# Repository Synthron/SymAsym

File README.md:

# SymAsym

High Power Audio Amplifier based on the Red Devil SymAsym PCBs from audiopcb.de

For complete system schematic of a stereo amplifier, refer to _**Overview_Schematic.pdf**_

Specs:  

- 350W @ 4 Ohm
- 185W @ 8 Ohm

Zusätzliches Empfangsmodul "Up2Stream Pro V3" empfohlen.

## Warenkörbe Reichelt

- [Black Devil Amplifier](https://www.reichelt.de/my/2100439) 
  - 2x benötigt für Stereo
  - Extra Kühlkörper benötigt - siehe unten
- [Netzfilter und Softstart](https://www.reichelt.de/my/2100481)
  - designed für Stereo, für Mono in der Mitte teilen
- [VU-Meter](https://www.reichelt.de/my/2100492)
- [Digital-Support](https://www.reichelt.de/my/2100502)
  - Extra OLED benötigt (I2C-Schnittstelle, siehe unten)

## Einstellung

- Vor Inbetriebnahme Poti so drehen, dass zwischen unterem Pin R24 und linkem Pin R9 500 Ohm Widerstand gemessen werden.  
- Kurzschlussbrücke am Signaleingang einstecken für Abgleich.  
- Spannung anschließen und am Ausgang messen, sollte ca. 0V betragen.  
- Jetzt Poti so lange drehen, bis zwischen TP1->TP3 und TP2->TP3 jeweils 55mV (0,055V) anliegen.  
- Fertig

## Anmerkungen

### Amplifier

**Wichtig!!!**  
Der Warenkorb ist nur für eine Platine! Für einen Stereo-Verstärker bitte zwei mal bestellen!

**2N5551 und 2N5401 Transistoren:**  
Anstatt passender Anzahl sind in den Warenkörben zu viele eingetragen. Dadurch hat man genug Transistoren um die drei notwendingen Paare matchen zu können. Siehe Schaltplan, welche Transistoren gematcht sein müssen.

**Kühlkörper**  
Die Leistungstransistoren müssen mit einer Glimmerscheibe gegen den Kühlkörper isoliert werden. Elektrisch isolierende Wärmeleitpads sind auch ok. Keinesfalls nur Wärmeleitpaste benutzen!

Beispiel [Silikonfolie](https://www.reichelt.de/silikon-isolierfolie-200x200x0-18mm-si-4018-p35416.html?&trstct=pos_1&nbc=1); [Glimmer TO220](https://www.reichelt.de/glimmerscheibe-fuer-gehaeuse-to-220-glimmer-to-220-p8194.html?&trstct=pos_5&nbc=1)  
Die Isolierbuchsen (im Warenkorb) müssen bei den MJE-Transistoren (TO220) verwendet werden!

**R7**  
Der Widerstand R7 muss mit 10 Windungen 0,7mm - 1mm Kupferlackdraht umwickelt werden, dieser wird an die Pins des Widerstandes angelötet. 

---

### Netzfilter und Softstart

Die Sicherungshalter sind einzelne Federn, beim Einlöten mit 5x20mm Feinsicherung ausrichten.  

---

### VU-Meter

Vorsicht: LEDs und Potis auf Rückseite und alles außer LEDs/Terminals ist SMD.

Zum Abgleichen: maximale gewollte Lautstärke aufdrehen, mit Potis so einstellen, dass nur die erste rote LED leuchtet.  
Für beide Kanäle einzeln einrichten.

---

### Digital-Support

Die Sicherungshalter sind einzelne Federn, beim Einlöten mit 5x20mm Feinsicherung ausrichten.  
Fast alle Bauteile sind SMD.

NTC-Widerstände werden direkt an die Kühlkörper geschraubt!

Die Bedienung erfolg neben dem Drehencoder über ein OLED, original wird [dieses](https://www.reichelt.de/entwicklerboards-display-oled-2-42-128x64-pixel-debo-oled-2-42-p335005.html?&trstct=pos_3&nbc=1) benutzt.

Wenn **kein** Up2Stream benutzt wird, PD2 und GND verbinden.

Konfiguration für Standard Eingang:

| Standard Eingang      | PD3 | PD4 |
|-----------------------|:---:|:---:|
| Kein Eingang          | GND | GND |
| Eingang 1 (Klinke)    |  5V | GND |
| Eingang 2 (Cinch)     | GND |  5V |
| Eingang 3 (Up2Stream) |  5V |  5V |

Der Kanal kann über den Drehencoder jederzeit geändert werden.  
Wenn das Up2Stream-Modul angeschlossen ist, werden je nach Möglichkeit aktuelle Song-Infos auf dem OLED angezeigt. 

---

### Gehäuse

Beim Entwurf wurde alles auf [dieses Gehäuse](https://www.reichelt.de/19-rack-gehaeuse-3-he-sin-3-he-sw-p247242.html?&trstct=pos_0&nbc=1) ausgelegt.

---

### Kühlkörper

Pro Verstärkerplatine sollte ein Kühlkörper mit maximal 0,5K/W vorgesehen werden. Für das oben genannte Gehäuse bietet sich [dieser Kühlkörper](https://www.reichelt.de/kuehlkoerper-100-mm-alu-0-4-k-w-sk-56-100-sa-p227981.html?&trstct=pol_5&nbc=1) an. Er ist 1cm zu lang, das kann aber zur Not gekürzt werden.

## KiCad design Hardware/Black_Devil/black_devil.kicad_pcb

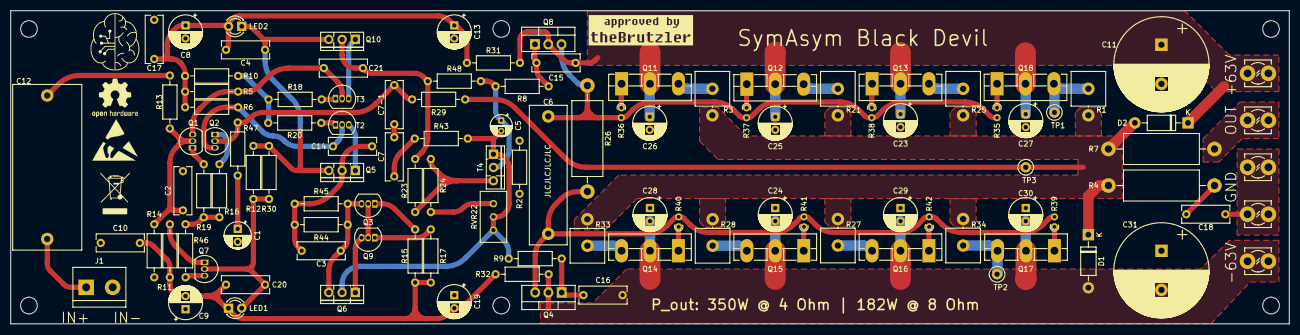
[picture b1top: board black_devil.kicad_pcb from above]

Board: 2 copper layers, 245.0 x 60.0 mm, 113 parts (0 on the bottom side), 60 nets.

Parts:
C1: 330µF/16V; CP_Radial_D5.0mm_P2.50mm
C2: 680p; C_Rect_L9.0mm_W3.2mm_P7.50mm_MKT
C3, C4, C10, C17, C20: 100n; C_Rect_L9.0mm_W3.2mm_P7.50mm_MKT
C5: 47µ/25V; CP_Radial_D4.0mm_P2.00mm
C6: 680n; C_Rect_L26.5mm_W7.0mm_P22.50mm_MKS4
C7, C7-1: 10p; C_Rect_L9.0mm_W3.2mm_P7.50mm_MKT
C8, C9, C13, C19, C23, C24, C25, C26, C27, C28, C29, C30: 22µ 100V; CP_Radial_D6.3mm_P2.50mm
C11, C31: 680µ 100V; CP_Radial_D18.0mm_P7.50mm
C12: 10µ; C_Rect_L31.5mm_W13.0mm_P27.50mm_MKS4
C14, C15, C16, C21: 100p; C_Rect_L9.0mm_W3.2mm_P7.50mm_MKT
C18: 47n; C_Rect_L9.0mm_W3.2mm_P7.50mm_MKT
D1, D2: 1N4004; D_DO-41_SOD81_P10.16mm_Horizontal
J1: Input; TerminalBlock_bornier-2_P5.08mm
J3: OUT; TerminalBlock_MetzConnect_360381_1x01_Horizontal_ScrewM3.0
J4: +63V; TerminalBlock_MetzConnect_360381_1x01_Horizontal_ScrewM3.0
J5: -63V; TerminalBlock_MetzConnect_360381_1x01_Horizontal_ScrewM3.0
J6: GND; TerminalBlock_MetzConnect_360381_1x01_Horizontal_ScrewM3.0
J7: SPK_GND; TerminalBlock_MetzConnect_360381_1x01_Horizontal_ScrewM3.0
LED1: RED; LED_D3.0mm
LED2: BLUE; LED_D3.0mm
Q1, Q2, Q3, Q7, Q9: 2N5551; TO-92_Inline
Q4: MJE15031; TO-220-3_Vertical
Q5, Q10: MJE350; TO-126-3_Vertical
Q6: MJE340; TO-126-3_Vertical
Q8: MJE15030; TO-220-3_Vertical
Q11, Q12, Q13, Q18: MJL3281; TO-3PB-3_Vertical
Q14, Q15, Q16, Q17: MJL1302; TO-3PB-3_Vertical
R1, R3, R21, R25, R27, R28, R33, R34: 0R22 5W; R_Axial_Power_L20.0mm_W6.4mm_P5.08mm_Vertical
R2: 10; R_Axial_DIN0207_L6.3mm_D2.5mm_P10.16mm_Horizontal
R4: 4R7 2W; R_Axial_DIN0614_L14.3mm_D5.7mm_P20.32mm_Horizontal
R5, R6: 1k; R_Axial_DIN0207_L6.3mm_D2.5mm_P10.16mm_Horizontal
R7: 10 2W; R_Axial_DIN0614_L14.3mm_D5.7mm_P20.32mm_Horizontal
R8, R9, R18, R20: 22; R_Axial_DIN0207_L6.3mm_D2.5mm_P10.16mm_Horizontal
R10: 120; R_Axial_DIN0207_L6.3mm_D2.5mm_P10.16mm_Horizontal
R11: 390; R_Axial_DIN0207_L6.3mm_D2.5mm_P10.16mm_Horizontal
R12, R30: 68k; R_Axial_DIN0207_L6.3mm_D2.5mm_P10.16mm_Horizontal
R13: 680; R_Axial_DIN0207_L6.3mm_D2.5mm_P10.16mm_Horizontal
R14, R29, R45: 22k; R_Axial_DIN0207_L6.3mm_D2.5mm_P10.16mm_Horizontal
R15, R17: 100; R_Axial_DIN0207_L6.3mm_D2.5mm_P10.16mm_Horizontal
R16, R19, R31, R32: 47; R_Axial_DIN0207_L6.3mm_D2.5mm_P10.16mm_Horizontal
R23: 1k5; R_Axial_DIN0207_L6.3mm_D2.5mm_P10.16mm_Horizontal
R24: 270; R_Axial_DIN0207_L6.3mm_D2.5mm_P10.16mm_Horizontal
R26: 68 2W; R_Axial_DIN0614_L14.3mm_D5.7mm_P20.32mm_Horizontal
R35, R36, R37, R38, R39, R40, R41, R42: 4R7; R_Axial_DIN0204_L3.6mm_D1.6mm_P1.90mm_Vertical
R43: 470; R_Axial_DIN0207_L6.3mm_D2.5mm_P10.16mm_Horizontal
R44: 15k; R_Axial_DIN0207_L6.3mm_D2.5mm_P10.16mm_Horizontal
R46: 10k; R_Axial_DIN0207_L6.3mm_D2.5mm_P10.16mm_Horizontal
R47: 820; R_Axial_DIN0207_L6.3mm_D2.5mm_P10.16mm_Horizontal
R48: 15; R_Axial_DIN0207_L6.3mm_D2.5mm_P10.16mm_Horizontal
RVR22: 500; Potentiometer_Bourns_3296W_Vertical
T2, T3: 2N5401; TO-92_Inline
T4: BD139; TO-126-3_Vertical
TP1: MP1; TestPoint_Loop_D2.50mm_Drill1.0mm
TP2, TP3: MP2; TestPoint_Loop_D2.50mm_Drill1.0mm

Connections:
+VDC: C11.1, C15.1, C23.1, C25.1, C26.1, C27.1, D2.1 (K), J4.1, Q8.2 (C), Q11.2 (C), Q12.2 (C), Q13.2 (C), Q18.2 (C), R31.2
-VDC: C16.2, C24.2, C28.2, C29.2, C30.2, C31.2, D1.2 (A), J5.1, Q4.2 (C), Q14.2 (C), Q15.2 (C), Q16.2 (C), Q17.2 (C), R32.2
/out: J3.1, R7.2
GND: C11.2, C18.2, C23.2, C24.1, C25.2, C26.2, C27.2, C28.1, C29.1, C30.1, C31.1, J6.1, J7.1, R2.2
GNDA: C1.2, C2.2, C8.2, C9.1, C10.1, C13.2, C17.2, C19.1, J1.2, R2.1, R14.2
unnamed: C1.1, R47.1
unnamed: C7.1, C7-1.2
unnamed: C7.2, R43.1
unnamed: C12.2, R13.1
unnamed: C18.1, R4.2
unnamed: D1.1 (K), D2.2 (A), R1.2, R3.2, R4.1, R7.1, R21.2, R25.2, R27.2, R28.2, R29.2, R33.2, R34.2, TP3.1
unnamed: C12.1, J1.1
unnamed: C20.1, LED1.2 (A), Q7.2 (B), R12.2, R30.2
unnamed: C9.2, C10.2, C19.2, C20.2, LED1.1 (K), R11.2, R15.2, R17.2, R32.1
unnamed: C4.1, C8.1, C13.1, C17.1, LED2.2 (A), R5.1, R6.1, R10.1, R31.1
unnamed: C4.2, LED2.1 (K), Q5.3 (B), Q10.3 (B), R12.1, R30.1
unnamed: C2.1, Q1.2 (B), R13.2, R14.1
unnamed: C21.1, Q1.3 (C), R5.2, T3.2 (B)
unnamed: Q1.1 (E), R19.1
unnamed: C7-1.1, Q2.2 (B), R29.1, R47.2
unnamed: C14.1, Q2.3 (C), R6.2, T2.2 (B)
unnamed: Q2.1 (E), R16.1
unnamed: Q3.2 (B), Q6.1 (E), Q9.2 (B), Q9.3 (C)
unnamed: C3.2, Q3.3 (C), Q6.3 (B), R44.2, R45.2
unnamed: Q3.1 (E), R15.1
unnamed: C16.1, Q4.1 (B), R9.2
unnamed: C6.2, Q4.3 (E), R26.2, R39.2, R40.2, R41.2, R42.2
unnamed: C3.1, C14.2, Q5.2 (C), R44.1, R45.1
unnamed: Q5.1 (E), T2.3 (C)
unnamed: C5.2, Q6.2 (C), R9.1, R43.2, RVR22.2, RVR22.3, T4.1 (E)
unnamed: Q7.3 (C), R46.2
unnamed: Q7.1 (E), R11.1
unnamed: C15.2, Q8.1 (B), R8.1
unnamed: C6.1, Q8.3 (E), R26.1, R35.2, R36.2, R37.2, R38.2
unnamed: Q9.1 (E), R17.1
unnamed: C21.2, Q10.2 (C), R23.1, R48.1
unnamed: Q10.1 (E), T3.3 (C)
unnamed: Q11.1 (B), R36.1
unnamed: Q11.3 (E), R3.1
unnamed: Q12.1 (B), R37.1
unnamed: Q12.3 (E), R21.1
unnamed: Q13.1 (B), R38.1
unnamed: Q13.3 (E), R25.1
unnamed: Q14.1 (B), R40.1
unnamed: Q14.3 (E), R33.1
unnamed: Q15.1 (B), R41.1
unnamed: Q15.3 (E), R28.1
unnamed: Q16.1 (B), R42.1
unnamed: Q16.3 (E), R27.1
unnamed: Q17.1 (B), R39.1
unnamed: Q17.3 (E), R34.1, TP2.1
unnamed: Q18.1 (B), R35.1
unnamed: Q18.3 (E), R1.1, TP1.1
unnamed: R10.2, R18.1, R20.2
unnamed: R16.2, R19.2, R46.1
unnamed: R24.2, RVR22.1
unnamed: R20.1, T2.1 (E)
unnamed: R18.2, T3.1 (E)
unnamed: R23.2, R24.1, T4.3 (B)
unnamed: C5.1, R8.2, R48.2, T4.2 (C)

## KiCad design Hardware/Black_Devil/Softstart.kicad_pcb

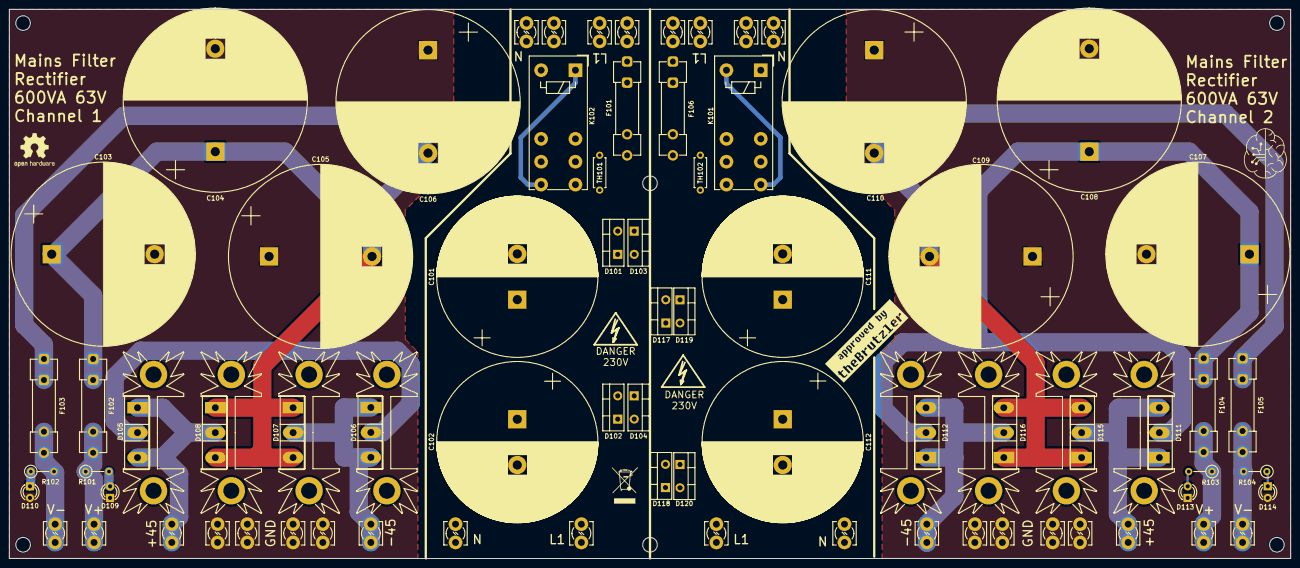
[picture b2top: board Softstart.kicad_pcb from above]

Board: 2 copper layers, 280.0 x 120.0 mm, 82 parts (0 on the bottom side), 30 nets.

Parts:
C101, C102, C111, C112: 22.000µ 40V; CP_Radial_D35.0mm_P10.00mm_SnapIn
C103, C104, C105, C106, C107, C108, C109, C110: 10.000µ 80V; CP_Radial_D40.0mm_P22,5
D101, D102, D103, D104, D117, D118, D119, D120: MUR860; TO-220-2_Vertical
D105, D106, D107, D108, D111, D112, D115, D116: MUR3020; TO-247-3_Vertical
D109, D110, D113, D114: LED; LED_D3.0mm
F101, F106: 3,15A; Fuseholder_Clip-5x20mm_Littelfuse_100_Inline_P20.50x4.60mm_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
F102, F103, F104, F105: 8A; Fuseholder_Clip-5x20mm_Littelfuse_100_Inline_P20.50x4.60mm_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
HS101, HS102, HS103, HS104, HS105, HS106, HS107, HS108: SK104; Heatsink_Fischer_SK104-STCB_35x13mm__2xDrill3.5mm_ScrewM3
J101, J113, J123, J125: L1; TerminalBlock_MetzConnect_360381_1x01_Horizontal_ScrewM3.0
J102, J104, J114, J126, J127, J128: N; TerminalBlock_MetzConnect_360381_1x01_Horizontal_ScrewM3.0
J103, J124: L1_F; TerminalBlock_MetzConnect_360381_1x01_Horizontal_ScrewM3.0
J105, J116: +45VAC; TerminalBlock_MetzConnect_360381_1x01_Horizontal_ScrewM3.0
J106, J119: -45VAC; TerminalBlock_MetzConnect_360381_1x01_Horizontal_ScrewM3.0
J107, J108, J120, J121: 0V; TerminalBlock_MetzConnect_360381_1x01_Horizontal_ScrewM3.0
J109, J115: +63VDC; TerminalBlock_MetzConnect_360381_1x01_Horizontal_ScrewM3.0
J110, J122: -63VDC; TerminalBlock_MetzConnect_360381_1x01_Horizontal_ScrewM3.0
J111, J112, J117, J118: GND; TerminalBlock_MetzConnect_360381_1x01_Horizontal_ScrewM3.0
K101, K102: FINDER-40.52; Relay_DPDT_Finder_40.52
R101, R102, R103, R104: 4k7 1W; R_Axial_DIN0207_L6.3mm_D2.5mm_P5.08mm_Vertical
TH101, TH102: EPC B57364-S100; R_Axial_DIN0207_L6.3mm_D2.5mm_P7.62mm_Horizontal

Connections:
GND1: C103.2, C104.2, C105.1, C106.1, D109.1 (K), D110.2 (A), J107.1, J108.1, J111.1, J112.1
GND2: C107.2, C108.2, C109.1, C110.1, D113.1 (K), D114.2 (A), J117.1, J118.1, J120.1, J121.1
unnamed: C105.2, C106.2, D107.1 (A), D107.3 (A), D108.1 (A), D108.3 (A), F103.1
unnamed: C109.2, C110.2, D115.1 (A), D115.3 (A), D116.1 (A), D116.3 (A), F105.1
unnamed: C101.2, D101.2 (A), D103.1 (K), K102.14, K102.24, K102.A1, TH101.1
unnamed: C101.1, C102.1, D101.1 (K), D102.2 (A), D103.2 (A), D104.1 (K)
unnamed: C102.2, D102.1 (K), D104.2 (A), J103.1
unnamed: C103.1, C104.1, D105.2 (K), D106.2 (K), F102.1
unnamed: D106.1 (A), D106.3 (A), D107.2 (K), J106.1
unnamed: D105.1 (A), D105.3 (A), D108.2 (K), J105.1
unnamed: D109.2 (A), R101.2
unnamed: D110.1 (K), R102.1
unnamed: C107.1, C108.1, D111.2 (K), D112.2 (K), F104.1
unnamed: D113.2 (A), R103.2
unnamed: D114.1 (K), R104.1
unnamed: D111.1 (A), D111.3 (A), D115.2 (K), J116.1
unnamed: D112.1 (A), D112.3 (A), D116.2 (K), J119.1
unnamed: C111.2, D117.2 (A), D119.1 (K), K101.14, K101.24, K101.A2, TH102.1
unnamed: C111.1, C112.1, D117.1 (K), D118.2 (A), D119.2 (A), D120.1 (K)
unnamed: C112.2, D118.1 (K), D120.2 (A), J124.1
unnamed: F101.2, K102.11, K102.21, TH101.2
unnamed: F106.2, K101.11, K101.21, TH102.2
unnamed: F101.1, J101.1, J113.1
unnamed: J102.1, J104.1, J114.1, K102.A2
unnamed: F102.2, J109.1, R101.1
unnamed: F103.2, J110.1, R102.2
unnamed: F104.2, J115.1, R103.1
unnamed: F105.2, J122.1, R104.2
unnamed: F106.1, J123.1, J125.1
unnamed: J126.1, J127.1, J128.1, K101.A1

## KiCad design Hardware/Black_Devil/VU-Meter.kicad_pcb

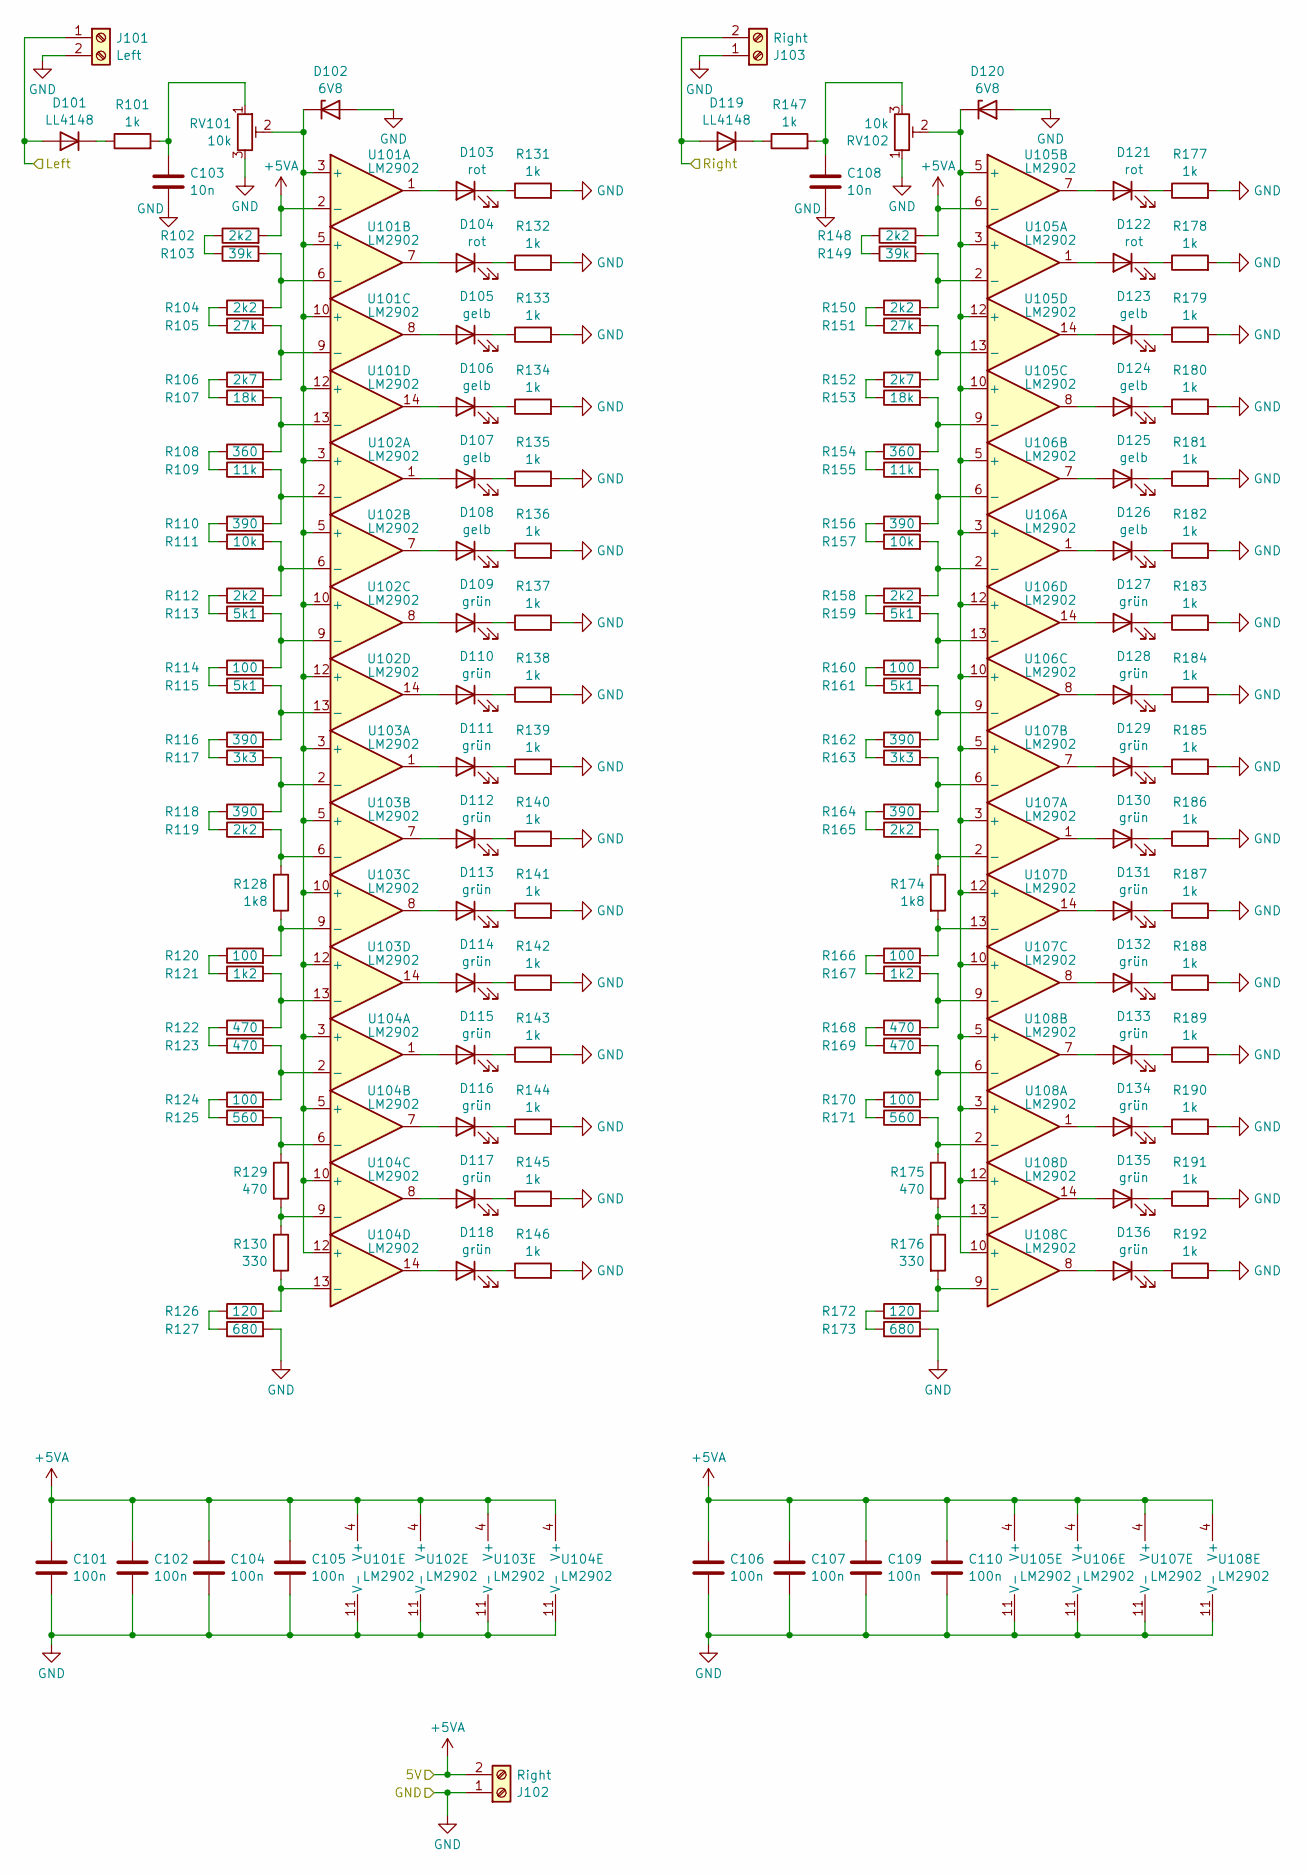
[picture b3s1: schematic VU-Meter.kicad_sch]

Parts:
C101, C102, C104, C105, C106, C107, C109, C110: 100n; C_0603_1608Metric
C103, C108: 10n; C_0603_1608Metric
D101, D119: LL4148; D_MiniMELF
D102, D120: 6V8; D_MiniMELF
D103, D104, D121, D122: rot; LED_D3.0mm_Clear
D105, D106, D107, D108, D123, D124, D125, D126: gelb; LED_D3.0mm_Clear
D109, D110, D111, D112, D113, D114, D115, D116, D117, D118, D127, D128, D129, D130, D131, D132, D133, D134, D135, D136: grün; LED_D3.0mm_Clear
J101: Left; TerminalBlock_bornier-2_P5.08mm
J102, J103: Right; TerminalBlock_bornier-2_P5.08mm
R101, R131, R132, R133, R134, R135, R136, R137, R138, R139, R140, R141, R142, R143, R144, R145, R146, R147, R177, R178, R179, R180, R181, R182, R183, R184, R185, R186, R187, R188, R189, R190, R191, R192: 1k; R_0603_1608Metric
R102, R104, R112, R119, R148, R150, R158, R165: 2k2; R_0603_1608Metric
R103, R149: 39k; R_0603_1608Metric
R105, R151: 27k; R_0603_1608Metric
R106, R152: 2k7; R_0603_1608Metric
R107, R153: 18k; R_0603_1608Metric
R108, R154: 360; R_0603_1608Metric
R109, R155: 11k; R_0603_1608Metric
R110, R116, R118, R156, R162, R164: 390; R_0603_1608Metric
R111, R157: 10k; R_0603_1608Metric
R113, R115, R159, R161: 5k1; R_0603_1608Metric
R114, R120, R124, R160, R166, R170: 100; R_0603_1608Metric
R117, R163: 3k3; R_0603_1608Metric
R121, R167: 1k2; R_0603_1608Metric
R122, R123, R129, R168, R169, R175: 470; R_0603_1608Metric
R125, R171: 560; R_0603_1608Metric
R126, R172: 120; R_0603_1608Metric
R127, R173: 680; R_0603_1608Metric
R128, R174: 1k8; R_0603_1608Metric
R130, R176: 330; R_0603_1608Metric
RV101, RV102: 10k; Potentiometer_Vishay_TS53YJ_Vertical
U101, U102, U103, U104, U105, U106, U107, U108: LM2902; TSSOP-14_4.4x5mm_P0.65mm

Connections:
+5VA: C101.1, C102.1, C104.1, C105.1, C106.1, C107.1, C109.1, C110.1, J102.2, R102.2, R148.2, U101.2 (-), U101.4 (V+), U102.4 (V+), U103.4 (V+), U104.4 (V+), U105.4 (V+), U105.6 (-), U106.4 (V+), U107.4 (V+), U108.4 (V+)
/Left: D101.2 (A), J101.1
/Right: D119.2 (A), J103.2
GND: C101.2, C102.2, C103.2, C104.2, C105.2, C106.2, C107.2, C108.2, C109.2, C110.2, D102.2 (A), D120.2 (A), J101.2, J102.1, J103.1, R127.2, R131.2, R132.2, R133.2, R134.2, R135.2, R136.2, R137.2, R138.2, R139.2, R140.2, R141.2, R142.2, R143.2, R144.2, R145.2, R146.2, R173.2, R177.2, R178.2, R179.2, R180.2, R181.2, R182.2, R183.2, R184.2, R185.2, R186.2, R187.2, R188.2, R189.2, R190.2, R191.2, R192.2, RV101.3, RV102.1, U101.11 (V-), U102.11 (V-), U103.11 (V-), U104.11 (V-), U105.11 (V-), U106.11 (V-), U107.11 (V-), U108.11 (V-)
unnamed: C103.1, R101.2, RV101.1
unnamed: C108.1, R147.2, RV102.3
unnamed: D101.1 (K), R101.1
unnamed: D102.1 (K), RV101.2, U101.3 (+), U101.5 (+), U101.10 (+), U101.12 (+), U102.3 (+), U102.5 (+), U102.10 (+), U102.12 (+), U103.3 (+), U103.5 (+), U103.10 (+), U103.12 (+), U104.3 (+), U104.5 (+), U104.10 (+), U104.12 (+)
unnamed: D103.2 (A), U101.1
unnamed: D103.1 (K), R131.1
unnamed: D104.2 (A), U101.7
unnamed: D104.1 (K), R132.1
unnamed: D105.2 (A), U101.8
unnamed: D105.1 (K), R133.1
unnamed: D106.2 (A), U101.14
unnamed: D106.1 (K), R134.1
unnamed: D107.2 (A), U102.1
unnamed: D107.1 (K), R135.1
unnamed: D108.2 (A), U102.7
unnamed: D108.1 (K), R136.1
unnamed: D109.2 (A), U102.8
unnamed: D109.1 (K), R137.1
unnamed: D110.2 (A), U102.14
unnamed: D110.1 (K), R138.1
unnamed: D111.2 (A), U103.1
unnamed: D111.1 (K), R139.1
unnamed: D112.2 (A), U103.7
unnamed: D112.1 (K), R140.1
unnamed: D113.2 (A), U103.8
unnamed: D113.1 (K), R141.1
unnamed: D114.2 (A), U103.14
unnamed: D114.1 (K), R142.1
unnamed: D115.2 (A), U104.1
unnamed: D115.1 (K), R143.1
unnamed: D116.2 (A), U104.7
unnamed: D116.1 (K), R144.1
unnamed: D117.2 (A), U104.8
unnamed: D117.1 (K), R145.1
unnamed: D118.2 (A), U104.14
unnamed: D118.1 (K), R146.1
unnamed: D119.1 (K), R147.1
unnamed: D120.1 (K), RV102.2, U105.3 (+), U105.5 (+), U105.10 (+), U105.12 (+), U106.3 (+), U106.5 (+), U106.10 (+), U106.12 (+), U107.3 (+), U107.5 (+), U107.10 (+), U107.12 (+), U108.3 (+), U108.5 (+), U108.10 (+), U108.12 (+)
unnamed: D121.2 (A), U105.7
unnamed: D121.1 (K), R177.1
unnamed: D122.2 (A), U105.1
unnamed: D122.1 (K), R178.1
unnamed: D123.2 (A), U105.14
unnamed: D123.1 (K), R179.1
unnamed: D124.2 (A), U105.8
unnamed: D124.1 (K), R180.1
unnamed: D125.2 (A), U106.7
unnamed: D125.1 (K), R181.1
unnamed: D126.2 (A), U106.1
unnamed: D126.1 (K), R182.1
unnamed: D127.2 (A), U106.14
unnamed: D127.1 (K), R183.1
unnamed: D128.2 (A), U106.8
unnamed: D128.1 (K), R184.1
unnamed: D129.2 (A), U107.7
unnamed: D129.1 (K), R185.1
unnamed: D130.2 (A), U107.1
unnamed: D130.1 (K), R186.1
unnamed: D131.2 (A), U107.14
unnamed: D131.1 (K), R187.1
unnamed: D132.2 (A), U107.8
unnamed: D132.1 (K), R188.1
unnamed: D133.2 (A), U108.7
unnamed: D133.1 (K), R189.1
unnamed: D134.2 (A), U108.1
unnamed: D134.1 (K), R190.1
unnamed: D135.2 (A), U108.14
unnamed: D135.1 (K), R191.1
unnamed: D136.2 (A), U108.8
unnamed: D136.1 (K), R192.1
unnamed: R102.1, R103.1
unnamed: R104.1, R105.1
unnamed: R106.1, R107.1
unnamed: R108.1, R109.1
unnamed: R110.1, R111.1
unnamed: R112.1, R113.1
unnamed: R114.1, R115.1
unnamed: R116.1, R117.1
unnamed: R118.1, R119.1
unnamed: R120.1, R121.1
unnamed: R122.1, R123.1
unnamed: R124.1, R125.1
unnamed: R126.1, R127.1
unnamed: R148.1, R149.1
unnamed: R150.1, R151.1
unnamed: R152.1, R153.1
unnamed: R154.1, R155.1
unnamed: R156.1, R157.1
unnamed: R158.1, R159.1
unnamed: R160.1, R161.1
unnamed: R162.1, R163.1
unnamed: R164.1, R165.1
unnamed: R166.1, R167.1
unnamed: R168.1, R169.1
unnamed: R170.1, R171.1
unnamed: R172.1, R173.1
unnamed: R103.2, R104.2, U101.6 (-)
unnamed: R105.2, R106.2, U101.9 (-)
unnamed: R107.2, R108.2, U101.13 (-)
unnamed: R109.2, R110.2, U102.2 (-)
unnamed: R111.2, R112.2, U102.6 (-)
unnamed: R113.2, R114.2, U102.9 (-)
unnamed: R115.2, R116.2, U102.13 (-)
unnamed: R117.2, R118.2, U103.2 (-)
unnamed: R119.2, R128.1, U103.6 (-)
unnamed: R120.2, R128.2, U103.9 (-)
unnamed: R121.2, R122.2, U103.13 (-)
unnamed: R123.2, R124.2, U104.2 (-)
unnamed: R125.2, R129.1, U104.6 (-)
unnamed: R129.2, R130.1, U104.9 (-)
unnamed: R126.2, R130.2, U104.13 (-)
unnamed: R149.2, R150.2, U105.2 (-)
unnamed: R153.2, R154.2, U105.9 (-)
unnamed: R151.2, R152.2, U105.13 (-)
unnamed: R157.2, R158.2, U106.2 (-)
unnamed: R155.2, R156.2, U106.6 (-)
unnamed: R161.2, R162.2, U106.9 (-)
unnamed: R159.2, R160.2, U106.13 (-)
unnamed: R165.2, R174.1, U107.2 (-)
unnamed: R163.2, R164.2, U107.6 (-)
unnamed: R167.2, R168.2, U107.9 (-)
unnamed: R166.2, R174.2, U107.13 (-)
unnamed: R171.2, R175.1, U108.2 (-)
unnamed: R169.2, R170.2, U108.6 (-)
unnamed: R172.2, R176.2, U108.9 (-)
unnamed: R175.2, R176.1, U108.13 (-)

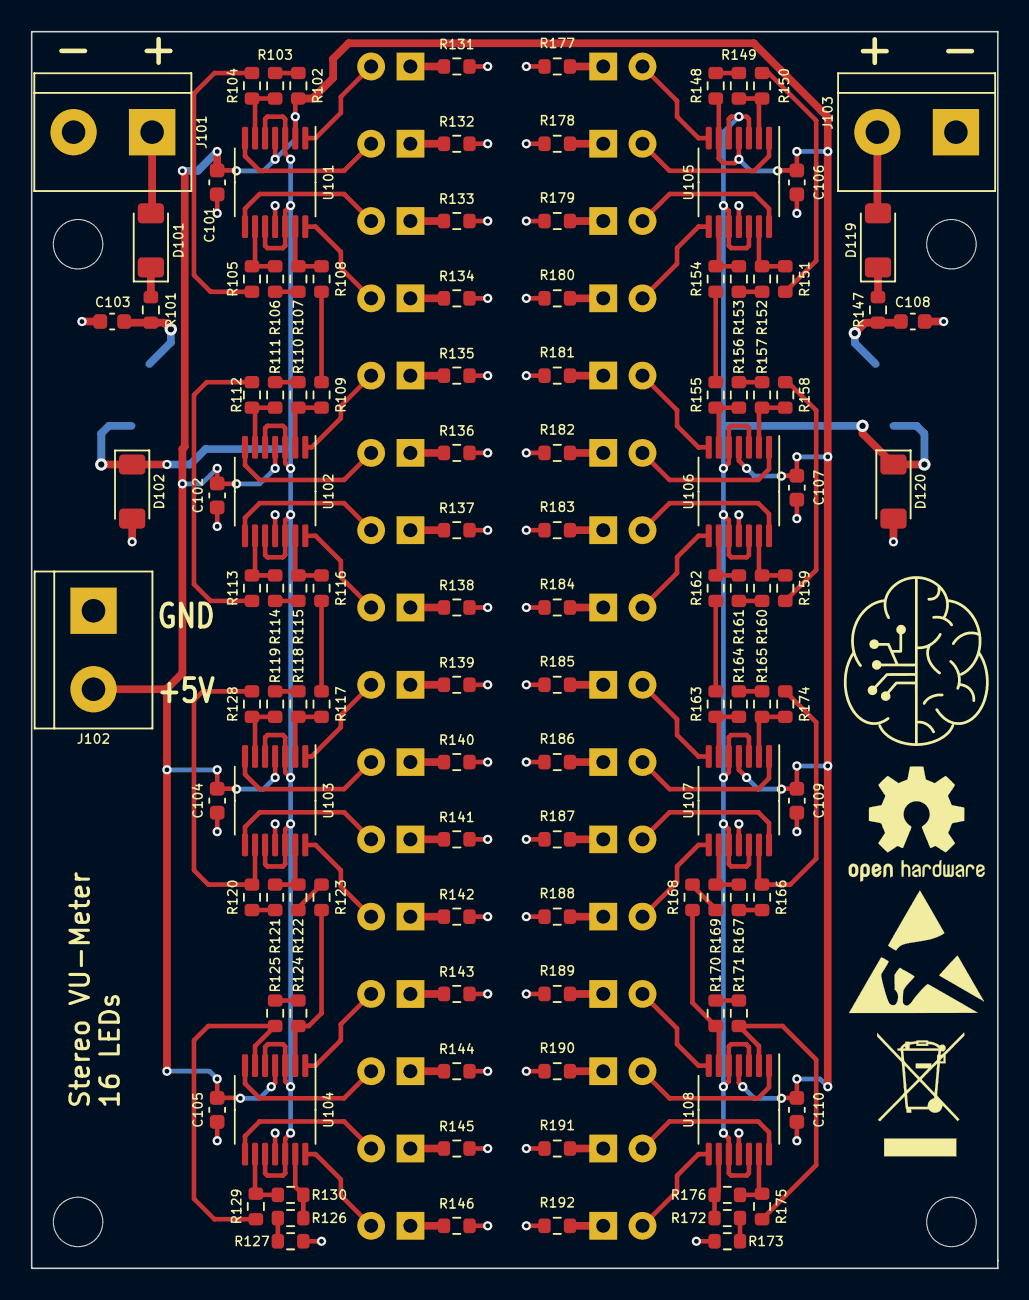
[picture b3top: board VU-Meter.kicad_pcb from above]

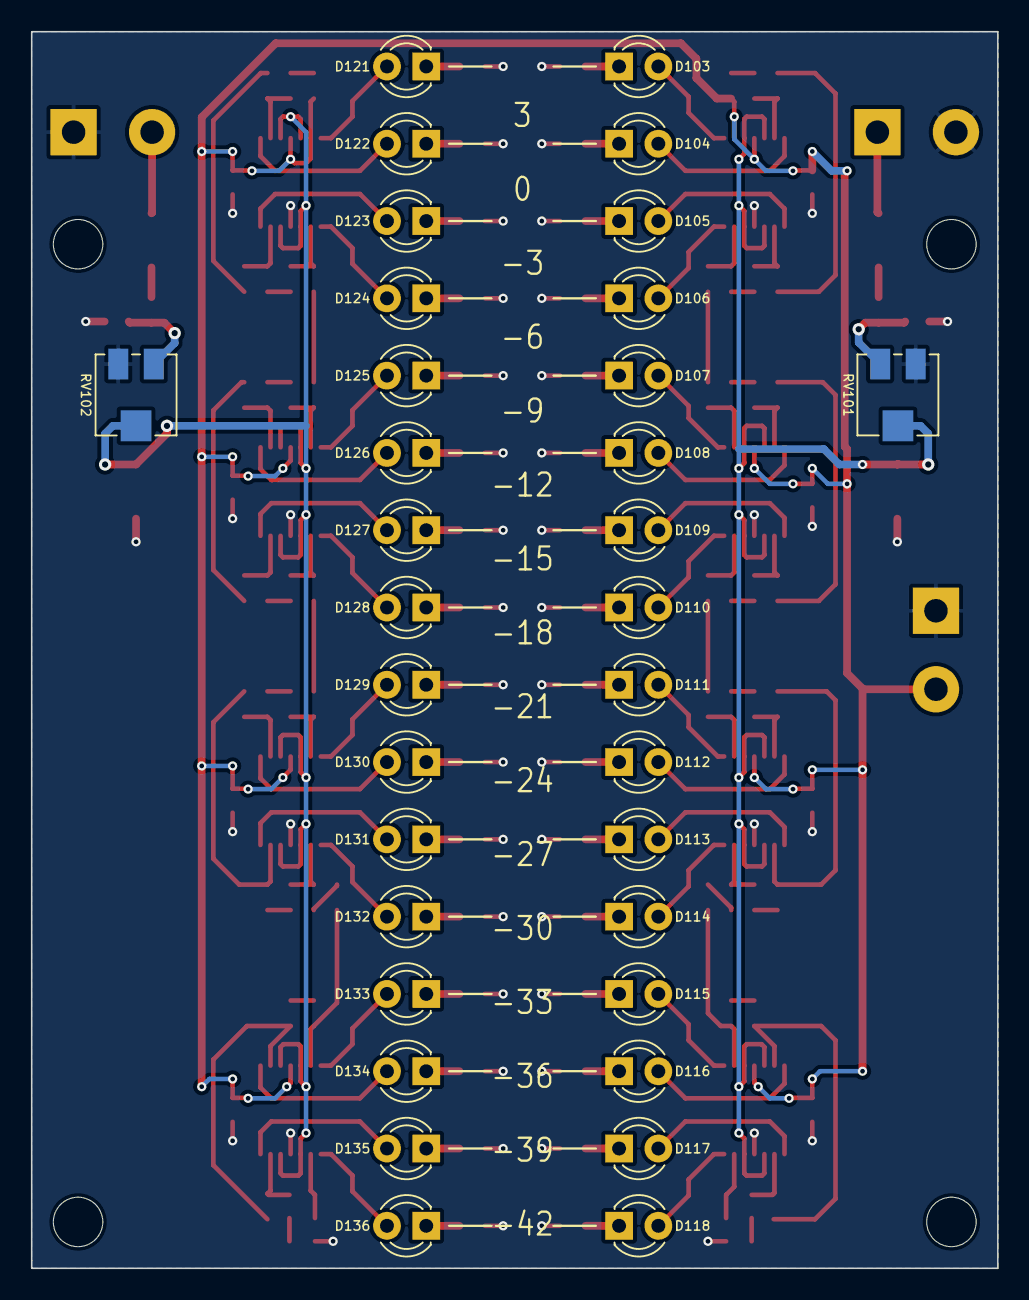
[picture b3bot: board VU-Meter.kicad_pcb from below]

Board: 2 copper layers, 62.5 x 80.0 mm, 151 parts (34 on the bottom side), 130 nets.

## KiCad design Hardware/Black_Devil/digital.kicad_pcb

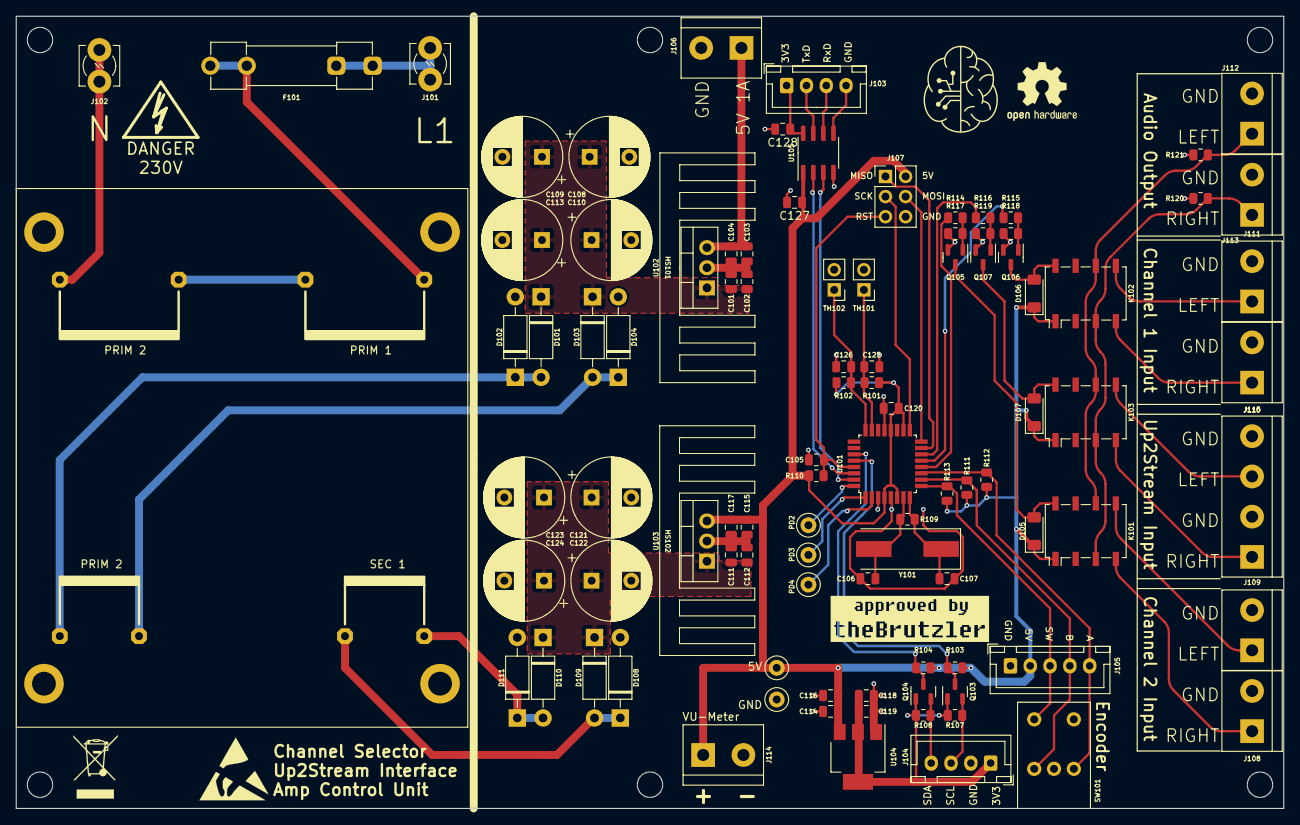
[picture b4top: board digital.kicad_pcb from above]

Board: 2 copper layers, 160.0 x 100.0 mm, 99 parts (0 on the bottom side), 56 nets.

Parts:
C101, C104, C111, C114, C117, C119, C125, C126: 1µ; C_0805_2012Metric
C102, C103, C105, C112, C115, C116, C118, C120, C127, C128: 100n; C_0805_2012Metric
C106, C107: 18p; C_0805_2012Metric
C108, C109, C110, C113, C121, C122, C123, C124: 470µ; CP_Radial_D10.0mm_P5.00mm
D101, D102, D103, D104, D108, D109, D110, D111: 1N4004; D_DO-41_SOD81_P10.16mm_Horizontal
D105, D106, D107: LL4148; D_MiniMELF
F101: 0,5A; Fuseholder_Clip-5x20mm_Littelfuse_100_Inline_P20.50x4.60mm_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
HS101, HS102: Heatsink; V 4330N
J101: L1; TerminalBlock_MetzConnect_360381_1x01_Horizontal_ScrewM3.0
J102: N; TerminalBlock_MetzConnect_360381_1x01_Horizontal_ScrewM3.0
J103, J104: OLED; JST_XH_B4B-XH-A_1x04_P2.50mm_Vertical
J105: Encoder; JST_XH_B5B-XH-A_1x05_P2.50mm_Vertical
J106: Up2Stream; TerminalBlock_bornier-2_P5.08mm
J107: ICSP; PinHeader_2x03_P2.54mm_Vertical
J108: Klinke_Right; TerminalBlock_bornier-2_P5.08mm
J109: Klinke_Links; TerminalBlock_bornier-2_P5.08mm
J110: Cinch_Right; TerminalBlock_bornier-2_P5.08mm
J111: Cinch_Left; TerminalBlock_bornier-2_P5.08mm
J112: Left; TerminalBlock_bornier-2_P5.08mm
J113: Right; TerminalBlock_bornier-2_P5.08mm
J114: VU-Meter; TerminalBlock_bornier-2_P5.08mm
J115: Up2Stream; TerminalBlock_bornier-4_P5.08mm
K101, K102, K103: G6K-2; Relay_DPDT_Omron_G6K-2F
Q103, Q104, Q105, Q106, Q107: BSS138; SOT-23
R101, R102, R103, R104, R107, R108: 4k7; R_0805_2012Metric
R109: 1M; R_0805_2012Metric
R110, R111, R112, R113, R114, R115, R116: 10k; R_0805_2012Metric
R117, R118, R119: 100k; R_0805_2012Metric
R120, R121: 470k; R_0805_2012Metric
SW101: RotaryEncoder_Switch; RotaryEncoder_Bourns_Horizontal_PEC09-2xxxF-Sxxxx
TH101, TH102: Thermistor_NTC; PinHeader_1x02_P2.54mm_Vertical
TP101: PD2; TestPoint_Loop_D2.50mm_Drill1.0mm
TP102: PD3; TestPoint_Loop_D2.50mm_Drill1.0mm
TP103: PD4; TestPoint_Loop_D2.50mm_Drill1.0mm
TP104, TP105: TestPoint; TestPoint_Loop_D2.50mm_Drill1.0mm
TR101: UI 39/10,2 209; BLOCK 14VA
U101: ATmega328P-A; TQFP-32_7x7mm_P0.8mm
U102, U103: L7805; TO-220-3_Vertical
U104: AP1117-33; SOT-223-3_TabPin2
U105: ADuM1201AR; SOIC-8_3.9x4.9mm_P1.27mm
Y101: 16MHz; Crystal_SMD_HC49-SD

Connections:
+3V3: C118.1, C119.1, J104.1, Q103.1 (G), Q104.1 (G), R107.1, R108.1, U104.2 (VO)
+5V: C114.1, C115.1, C116.1, C117.1, C120.1, C127.1, D105.1 (K), D106.1 (K), D107.1 (K), J105.2, J107.2, J114.1, K101.1, K102.1, K103.1, R101.1, R102.2, R103.1, R104.1, R110.1, R111.1, R112.1, R113.1, TP105.1, U101.4 (VCC), U101.6 (VCC), U101.18 (AVCC), U101.20 (AREF), U103.3 (OUT), U104.3 (VI), U105.1 (VDD1)
+5VA: C103.1, C104.1, J106.1, U102.3 (OUT)
+12V: C111.1, C112.1, C121.1, C122.1, C123.1, C124.1, D108.1 (K), D110.1 (K), U103.1 (IN)
+12VA: C101.1, C102.1, C108.1, C109.1, C110.1, C113.1, D101.1 (K), D103.1 (K), U102.1 (IN)
/L1: F101.1, J101.1
/Left: J112.1, K101.6, K102.6, K103.6, R121.1
/N: J102.1, TR101.4
/Right: J113.1, K101.3, K102.3, K103.3, R120.1
/Sig_GND: J108.2, J109.2, J110.2, J111.2, J112.2, J113.2, J115.2, J115.4, R120.2, R121.2
GND: C105.2, C106.1, C107.1, C111.2, C112.2, C114.2, C115.2, C116.2, C117.2, C118.2, C119.2, C120.2, C121.2, C122.2, C123.2, C124.2, C125.1, C126.2, C127.2, D109.2 (A), D111.2 (A), J104.2, J105.1, J107.6, J114.2, Q105.2 (S), Q106.2 (S), Q107.2 (S), R117.2, R118.2, R119.2, SW101.C, SW101.S2, TH101.2, TH102.2, TP104.1, U101.3 (GND), U101.5 (GND), U101.21 (GND), U103.2 (GND), U104.1 (GND), U105.4 (GND1)
GND1: C101.2, C102.2, C103.2, C104.2, C108.2, C109.2, C110.2, C113.2, C128.2, D102.2 (A), D104.2 (A), J103.4, J106.2, U102.2 (GND), U105.5 (GND2)
MISO: J107.1, U101.15 (PB3)
MOSI: J107.4, U101.16 (PB4)
NTC1: C125.2, R101.2, TH101.1, U101.23 (PC0)
NTC2: C126.1, R102.1, TH102.1, U101.24 (PC1)
unnamed: D101.2 (A), D102.1 (K), TR101.8
unnamed: D103.2 (A), D104.1 (K), TR101.7
unnamed: D105.2 (A), K101.8, Q105.3 (D)
unnamed: D106.2 (A), K102.8, Q106.3 (D)
unnamed: D107.2 (A), K103.8, Q107.3 (D)
unnamed: D108.2 (A), D109.1 (K), TR101.6
unnamed: D110.2 (A), D111.1 (K), TR101.5
unnamed: F101.2, TR101.1
unnamed: C128.1, J103.1, U105.8 (VDD2)
unnamed: J103.2, U105.7 (VIA)
unnamed: J103.3, U105.6 (VOB)
unnamed: J104.3, Q103.2 (S), R107.2
unnamed: J104.4, Q104.2 (S), R108.2
unnamed: J105.3, R113.2, SW101.S1, U101.9 (PD5)
unnamed: J105.4, R111.2, SW101.A, U101.10 (PD6)
unnamed: J105.5, R112.2, SW101.B, U101.11 (PD7)
unnamed: J108.1, K101.4
unnamed: J109.1, K101.5
unnamed: J110.1, K102.4
unnamed: J111.1, K102.5
unnamed: J115.1, K103.4
unnamed: J115.3, K103.5
unnamed: Q105.1 (G), R114.2, R117.1
unnamed: Q106.1 (G), R115.2, R118.1
unnamed: Q107.1 (G), R116.2, R119.1
unnamed: TR101.2, TR101.3
unnamed: R114.1, U101.12 (PB0)
unnamed: R115.1, U101.13 (PB1)
unnamed: R116.1, U101.14 (PB2)
unnamed: TP101.1, U101.32 (PD2)
unnamed: TP102.1, U101.1 (PD3)
unnamed: TP103.1, U101.2 (PD4)
unnamed: C106.2, R109.1, U101.7 (XTAL1/PB6), Y101.2
unnamed: C107.2, R109.2, U101.8 (XTAL2/PB7), Y101.1
RST: C105.1, J107.5, R110.2, U101.29 (~RESET/PC6)
RxD: U101.30 (PD0), U105.2 (VOA)
SCK: J107.3, U101.17 (PB5)
SCL: Q103.3 (D), R103.2, U101.28 (PC5)
SDA: Q104.3 (D), R104.2, U101.27 (PC4)
TxD: U101.31 (PD1), U105.3 (VIB)

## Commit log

2022-10-04 update schematic
2023-10-29 major update
2023-10-30 VU-Meter Update
    added correct values for log scale in 3dB steps
    started layout
2023-10-31 Major Update
    Repo Cleanup
    Finished VU Meter PCB
    Finalized Softstart PCB
    Finalized Channel PCB
2023-10-31 Readme Update
2023-11-01 Finalize all PCBs
2023-11-01 rounding tracks on audio side
2023-11-14 Reviews
2023-11-16 Reviews, Gerber Plots and Overview Update
2023-11-19 Readme and Overview Update
2023-11-21 add tube amp schematics
